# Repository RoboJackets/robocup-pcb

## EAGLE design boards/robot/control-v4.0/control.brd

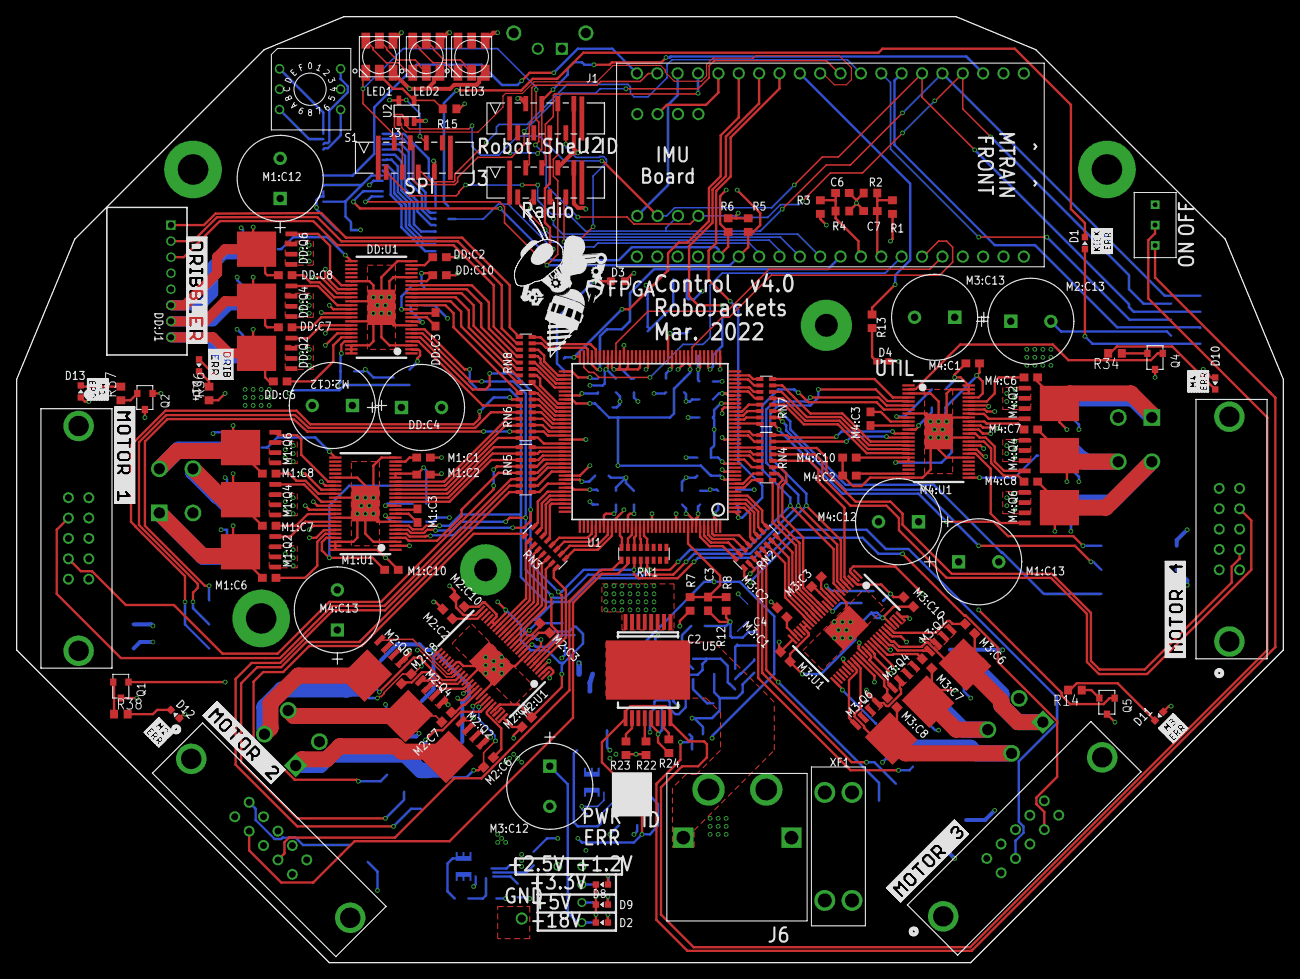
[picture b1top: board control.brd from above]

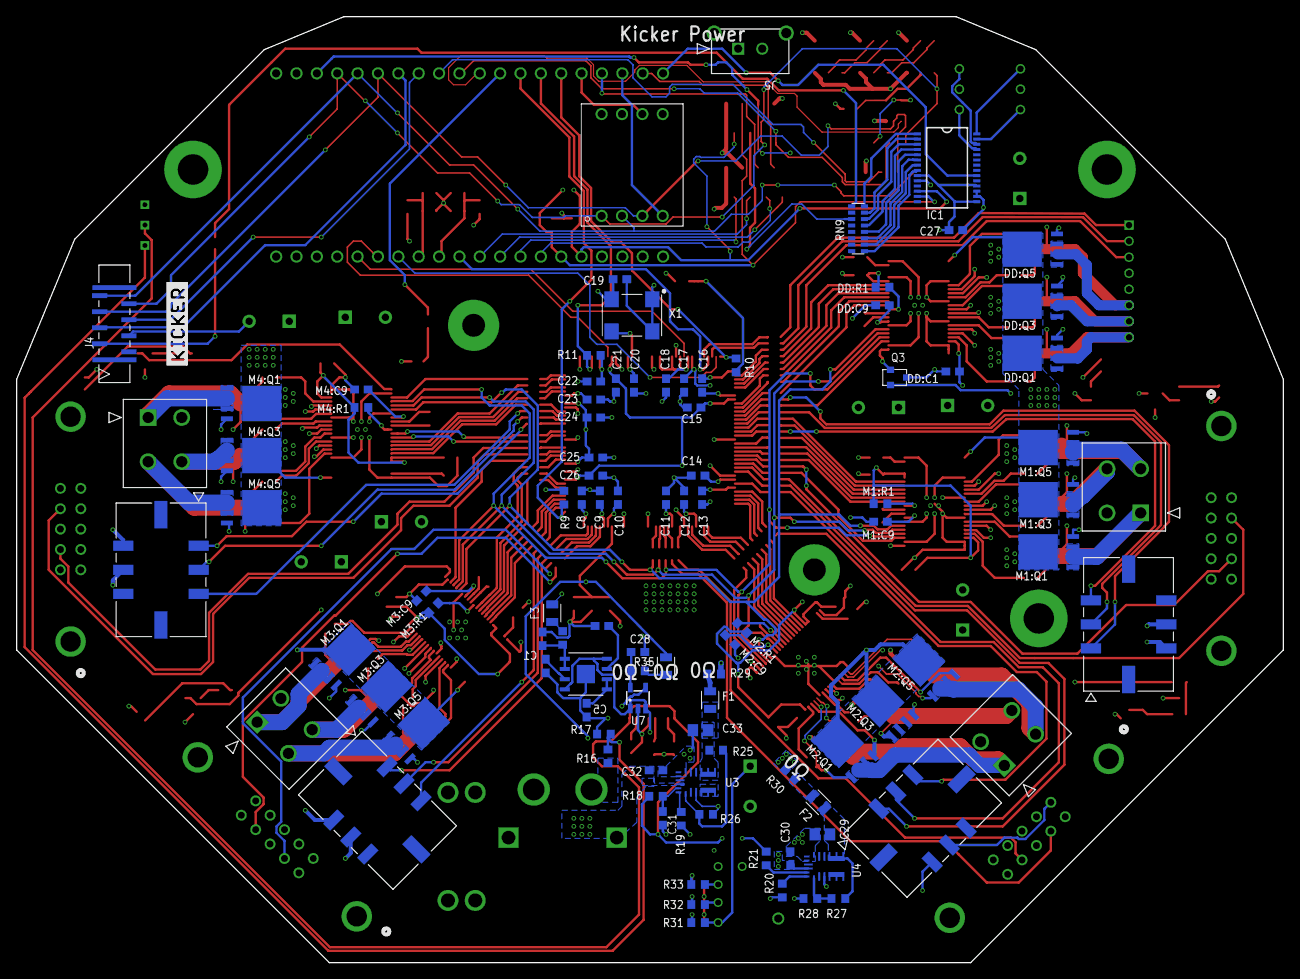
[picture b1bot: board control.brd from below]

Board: 6 copper layers, 158.0 x 118.0 mm, 238 parts (100 on the bottom side), 312 nets.

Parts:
C1, C2, C5, C28: 1uF; C0603
C3, C6, C8, C9, C10, C11, C12, C13, C14, C15, C16, C17, C18, C19, C20, C21, C22, C23, C24, C25, C26, C27: 0.1uF; C0603
C4: 10uF; C0603
C7: 0.1uF 50V; C0603
C29, C33: 22uF 16V; C0805
C30, C32: GRM188R6YA106MA73D; C0603
C31: 2.2uF 50V; C0603
D1, D10, D11, D12, D13, D14: RED; CHIP-LED0603
D2, D8, D9: GREEN; CHIP-LED0603
D3: BLUE; LED-0603
D4: BLUE; CHIP-LED0603
DD:C1, DD:C2: 1uF; C0603
DD:C3: 0.022uF 50V; C0603
DD:C4: ECA-1HHG221; CAP_PAN_10X12.5
DD:C6, DD:C7, DD:C8, DD:C10: 0.1uF 50V; C0603
DD:C9: 2.2uF 50V; C0603
DD:J1: 8-PIN_2MM-H; 2MM-8-H
DD:Q1, DD:Q2, DD:Q3, DD:Q4, DD:Q5, DD:Q6: IRFH7545; PQFN_5X6_E
DD:R1: 10k; R0603
DD:U1: DRV8303DCA; TSSOP-48_PAD
F1, F2, F3, F4: 0805L200SLTHYR; FUSC2113X75
IC1: MCP23017-E/SS; SSOP-28
J1, J2, J3, J4: SFW8S-2STE1LF; CON8_1X8_UB_SFW_JAE
J5: 436500217; CON_436500217_MOL
J6: XT60PW-MAMASS; XT60PW-M
KIT1: MTRAIN; MTRAIN-KIT
KIT2: IMU
LED1, LED2, LED3: APA102C-5050; APA102_5050
M1:C1, M1:C2, M2:C1, M2:C2, M3:C1, M3:C2, M4:C1, M4:C2: 1uF; C0603
M1:C3, M2:C3, M3:C3, M4:C3: 0.022uF 50V; C0603
M1:C6, M1:C7, M1:C8, M1:C10, M2:C6, M2:C7, M2:C8, M2:C10, M3:C6, M3:C7, M3:C8, M3:C10, M4:C6, M4:C7, M4:C8, M4:C10: 0.1uF 50V; C0603
M1:C9, M2:C9, M3:C9, M4:C9: 2.2uF 50V; C0603
M1:C12, M1:C13, M2:C12, M2:C13, M3:C12, M3:C13, M4:C12, M4:C13: ECA-1HHG221; CAP_PAN_10X12.5
M1:J1, M2:J1, M3:J1, M4:J1: 430450618; CON_430450618_MOL
M1:J2, M2:J2, M3:J2, M4:J2: 39288040; CON_39288040
M1:Q1, M1:Q2, M1:Q3, M1:Q4, M1:Q5, M1:Q6, M2:Q1, M2:Q2, M2:Q3, M2:Q4, M2:Q5, M2:Q6, M3:Q1, M3:Q2, M3:Q3, M3:Q4, M3:Q5, M3:Q6, M4:Q1, M4:Q2, M4:Q3, M4:Q4, M4:Q5, M4:Q6: IRFH7545; PQFN_5X6_E
M1:R1, M2:R1, M3:R1, M4:R1: 10k; R0603
M1:U1, M2:U1, M3:U1, M4:U1: DRV8303DCA; TSSOP-48_PAD
M1:U2, M2:U2, M3:U2, M4:U2: N3793-6303RB; N3793-6303RB_3MM
Q1, Q2, Q3, Q4, Q5: PJA3439_R1_00001; SOT-23
R1: 68k 1%; R0603
R2, R3, R4: 10k 1%; R0603
R5, R6, R9, R11: 4.7k; R0603
R7: 68k; R0603
R8, R22: 10k; R0603
R10, R13: 270; R0603
R12, R29, R30, R35: 0; R0603
R14, R34, R36, R37, R38: 330; R0603
R15: 50k; R0603
R16: 270k; R0603
R17: 100k; R0603
R18, R21: 150k; R0603
R19: 43.2k; R0603
R20: 29.4k; R0603
R23, R24, R31, R32, R33: 1k; R0603
R25, R27: 160k 1%; R0603
R26: 30.1k 1%; R0603
R28: 51.0k 1%; R0603
RN1, RN2, RN3, RN4, RN5, RN6, RN7, RN8, RN9: 330; RA-8_2506
S1: 94HCB16T; HEX
S3: TT11EGPC1
U1: XC3S250E-4TQG144C; TQFP144
U2: SN74AHC1G125; SOT-23-5
U3, U4: MPM3620GQV-P
U5: VND5E006ASPTR-E; POWERSO-16
U6: ADP7158ARDZ-1.2-R7ADP7158ARDZ-1.2-R7_ADI-L; ADP7158ARDZ-1.2-R7_ADI-L
U7: MCP1824T-2502E/OT; SOT-23-5
U$1: ERR-DRIB
U$3: MOTOR-1
U$4: DRIBBLER
U$5: MOTOR-2
U$6: MOTOR-3
U$7: MOTOR-4
U$8: ERR-M1
U$9: KICKER
U$11: ROBOBUZZ_1.0X2
U$12: ERR-M2
U$13: ERR-M3
U$14: ERR-M4
U$15: ERR-KICK
X1: ASV-18.432MHZ-EJ-T; ASV
XF1: 30A; 3557-2

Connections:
5V-LED: D9.A, R32.2
5V-LED1: D8.A, R33.2
18.5V-LED: D2.A, R31.1
!CS!-DOT: KIT1.P$11, U2.1
!CS!-FPGA: KIT1.P$31, U1.69
!CS!-ICM: KIT1.P$18, KIT2.4
!CS!-IR: J3.4, KIT1.P$10
!CS!-KICK: J4.5, KIT1.P$8
!CS!-RAD0: J2.4, KIT1.P$17
!RST!-I2C: J1.5, RN9.11
!RST!-IR: J3.5, KIT1.P$9
!RST!-KICK: J4.4, KIT1.P$7
!RST!-RADIO: J2.2, KIT1.P$19
+1.2V: C12.1, C15.1, C21.1, C26.1, F3.2, U1.9, U1.45, U1.80, U1.115
+1.2V-PRE: C4.1, R12.1, U6.1, U6.2
+2.5V: C10.1, C13.1, C17.1, C23.1, F4.2, R9.2, U1.30, U1.65, U1.102, U1.137
+2.5V-PRE: C28.1, R35.1, U7.5
+3.3V: C8.1, C9.1, C11.1, C14.1, C16.1, C18.1, C19.1, C20.1, C22.1, C24.1, C25.1, C27.1, D1.A, D10.A, D11.A, D12.A, D13.A, D14.A, DD:C1.1, DD:C10.1, DD:R1.1, DD:U1.19, DD:U1.45, IC1.9, IC1.15, IC1.18, J3.6, J4.2, KIT2.8, R5.2, R6.2, R11.1, R30.2, R33.1, U1.13, U1.28, U1.42, U1.49, U1.57, U1.60, U1.62, U1.64, U1.79, U1.100, U1.121, U1.138, U1.143, U2.5, U6.4, U6.8, U7.1, U7.3, X1.1, X1.4
+3.3V-FUSE: C29.1, F2.1, R27.2, U4.789
+5V: DD:J1.5, J1.8, J2.6, KIT1.VIN, LED1.1, LED2.1, LED3.1, M1:J1.5, M1:U2.9, M2:J1.5, M2:U2.9, M3:J1.5, M3:U2.9, M4:J1.5, M4:U2.9, R3.1, R29.2, R32.1
+5V-FUSE: C33.1, F1.1, R25.2, U3.789
+18.5V: C30.1, C32.1, DD:C4.1, DD:Q1.5678, DD:Q3.5678, DD:Q5.5678, DD:U1.25, M1:C12.1, M1:C13.1, M1:Q1.5678, M1:Q3.5678, M1:Q5.5678, M1:U1.25, M2:C12.1, M2:C13.1, M2:Q1.5678, M2:Q3.5678, M2:Q5.5678, M2:U1.25, M3:C12.1, M3:C13.1, M3:Q1.5678, M3:Q3.5678, M3:Q5.5678, M3:U1.25, M4:C12.1, M4:C13.1, M4:Q1.5678, M4:Q3.5678, M4:Q5.5678, M4:U1.25, R1.1, R7.1, R31.2, U3.16, U4.16, XF1.3, XF1.4
AAM: R19.2, U3.18
AAM1: R20.2, U4.18
BATT-FPGA: C3.1, R7.2, R8.1, U1.136
BYP: C1.1, U6.3
CS1: R23.2, U5.10
CS2: R24.2, U5.15
CS-DIS: R22.2, U5.12
DD-!CS: DD:U1.4, RN6.11
DD-!FAULT!: DD:U1.2, Q3.1
DD-A-H: DD:U1.13, RN6.9
DD-A-L: DD:U1.14, RN8.16
DD-B-H: DD:U1.15, RN8.15
DD-B-L: DD:U1.16, RN8.14
DD-C-H: DD:U1.17, RN8.13
DD-C-L: DD:U1.18, RN8.12
DD-H1: DD:J1.3, RN8.11
DD-H2: DD:J1.2, RN8.10
DD-H3: DD:J1.1, RN8.9
DD:AVDD: DD:C2.1, DD:U1.23
DD:BST-A: DD:C6.1, DD:U1.44
DD:BST-B: DD:C7.1, DD:U1.39
DD:BST-C: DD:C8.1, DD:U1.34
DD:CP1: DD:C3.1, DD:U1.10
DD:CP2: DD:C3.2, DD:U1.11
DD:EN-GATE: DD:R1.2, DD:U1.12
DD:GH-A: DD:Q1.4, DD:U1.43
DD:GH-B: DD:Q3.4, DD:U1.38
DD:GH-C: DD:Q5.4, DD:U1.33
DD:GL-A: DD:Q2.4, DD:U1.41
DD:GL-B: DD:Q4.4, DD:U1.36
DD:GL-C: DD:Q6.4, DD:U1.31
DD:GVDD: DD:C9.1, DD:U1.9
DD:PHASE-A: DD:C6.2, DD:J1.8, DD:Q1.1, DD:Q1.2, DD:Q1.3, DD:Q2.5678, DD:U1.42
DD:PHASE-B: DD:C7.2, DD:J1.7, DD:Q3.1, DD:Q3.2, DD:Q3.3, DD:Q4.5678, DD:U1.37
DD:PHASE-C: DD:C8.2, DD:J1.6, DD:Q5.1, DD:Q5.2, DD:Q5.3, DD:Q6.5678, DD:U1.32
DOT-CLK-1: LED1.5, R15.2, U2.4
DOT-CLK-1-2: LED1.2, LED2.5
DOT-CLK-2-3: LED2.2, LED3.5
DOT-MOSI-1-2: LED1.3, LED2.4
DOT-MOSI-2-3: LED2.3, LED3.4
EN: C31.1, R18.2, U3.17
EN1: R21.2, U4.17
EN-PWR: R18.1, R21.1, S3.3, U5.9, U5.16
EN-PWR-PRE: R16.1, R17.2, S3.2
EXTRA-IND: KIT1.P$12, R13.1
FB: R25.1, R26.2, U3.1
FB1: R27.1, R28.2, U4.1
FPGA-CLK: U1.50, X1.3
FPGA-DONE: KIT1.P$15, R10.1, U1.72
FPGA-INIT: KIT1.P$14, R11.2, U1.40
FPGA-PROG: KIT1.P$13, R9.1, U1.1
GND: C1.2, C2.2, C3.2, C4.2, C5.2, C6.2, C7.2, C8.2, C9.2, C10.2, C11.2, C12.2, C13.2, C14.2, C15.2, C16.2, C17.2, C18.2, C19.2, C20.2, C21.2, C22.2, C23.2, C24.2, C25.2, C26.2, C27.2, C28.2, C29.2, C30.2, C31.2, C32.2, C33.2, D2.C, D3.C, D4.C, D8.C, D9.C, DD:C1.2, DD:C2.2, DD:C4.2, DD:C9.2, DD:C10.2, DD:J1.4, DD:Q2.1, DD:Q2.2, DD:Q2.3, DD:Q4.1, DD:Q4.2, DD:Q4.3, DD:Q6.1, DD:Q6.2, DD:Q6.3, DD:U1.3, DD:U1.8, DD:U1.20, DD:U1.24, DD:U1.30, DD:U1.35, DD:U1.40, DD:U1.46, DD:U1.47, DD:U1.48, DD:U1.PAD, IC1.10, IC1.16, IC1.17, J1.2, J2.8, J3.7, J4.3, J5.2, J6.P$1, J6.P$3, KIT1.GND, KIT2.5, LED1.6, LED2.6, LED3.6, M1:C1.2, M1:C2.2, M1:C9.2, M1:C10.2, M1:C12.2, M1:C13.2, M1:J1.4, M1:Q2.1, M1:Q2.2, M1:Q2.3, M1:Q4.1, M1:Q4.2, M1:Q4.3, M1:Q6.1, M1:Q6.2, M1:Q6.3, M1:U1.3, M1:U1.8, M1:U1.24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
GPB0: IC1.1, RN9.8
GPB1: IC1.2, RN9.7
GPB2: IC1.3, RN9.6
GPB3: IC1.4, RN9.5
GPB4: IC1.5, RN9.4
GPB5: IC1.6, RN9.3
GPB6: IC1.7, RN9.2
GPB7: IC1.8, RN9.1
HEX-0: IC1.28, S1.1
HEX-1: IC1.25, S1.2
HEX-2: IC1.27, S1.4
HEX-3: IC1.26, S1.8
INT-I2C: J1.4, KIT1.P$3
INT-ICM: KIT1.P$16, KIT2.6
INT-IO: IC1.20, KIT1.P$20
INT-RAD0: J2.5, KIT1.P$30
LED-DD: D14.C, R36.2
LED-KICK: D1.C, RN9.9
LED-M1: D13.C, R37.2
LED-M2: D12.C, R38.2
LED-M3: D11.C, R14.2
LED-M4: D10.C, R34.2
M1-!CS: M1:U1.4, RN5.13
M1-!FAULT!: M1:U1.2, Q2.1
M1-A-H: M1:U1.15, RN5.9
M1-A-L: M1:U1.16, RN6.16
M1-B-H: M1:U1.13, RN5.11
M1-B-L: M1:U1.14, RN5.10
M1-C-H: M1:U1.17, RN6.14
M1-C-L: M1:U1.18, RN6.13
M1-ENC-A: M1:U2.8, RN5.14
M1-ENC-B: M1:U2.4, RN5.12
M1-H1: M1:J1.1, RN6.10
M1-H2: M1:J1.2, RN6.12
M1-H3: M1:J1.3, RN6.15
M1:+3.3V: M1:C1.1, M1:C10.1, M1:R1.1, M1:U1.19, M1:U1.20, M1:U1.45
M1:AVDD: M1:C2.1, M1:U1.23
M1:BST-A: M1:C6.1, M1:U1.44
M1:BST-B: M1:C7.1, M1:U1.39
M1:BST-C: M1:C8.1, M1:U1.34
M1:CP1: M1:C3.1, M1:U1.10
M1:CP2: M1:C3.2, M1:U1.11
M1:EN-GATE: M1:R1.2, M1:U1.12
M1:GH-A: M1:Q1.4, M1:U1.43
M1:GH-B: M1:Q3.4, M1:U1.38
M1:GH-C: M1:Q5.4, M1:U1.33
M1:GL-A: M1:Q2.4, M1:U1.41
M1:GL-B: M1:Q4.4, M1:U1.36
M1:GL-C: M1:Q6.4, M1:U1.31
M1:GVDD: M1:C9.1, M1:U1.9
M1:PHASE-A: M1:C7.2, M1:J2.4, M1:Q3.1, M1:Q3.2, M1:Q3.3, M1:Q4.5678, M1:U1.37
M1:PHASE-B: M1:C6.2, M1:J2.1, M1:Q1.1, M1:Q1.2, M1:Q1.3, M1:Q2.5678, M1:U1.42
M1:PHASE-C: M1:C8.2, M1:J2.3, M1:Q5.1, M1:Q5.2, M1:Q5.3, M1:Q6.5678, M1:U1.32
M2-!CS: M2:U1.4, RN3.16
M2-!FAULT!: M2:U1.2, Q1.1
M2-A-H: M2:U1.15, RN3.13
M2-A-L: M2:U1.16, RN3.12
M2-B-H: M2:U1.13, RN3.15
M2-B-L: M2:U1.14, RN3.14
M2-C-H: M2:U1.17, RN3.11
M2-C-L: M2:U1.18, RN3.10
M2-ENC-A: M2:U2.8, RN1.10
M2-ENC-B: M2:U2.4, RN1.9
M2-H1: M2:J1.1, RN5.15
M2-H2: M2:J1.2, RN5.16
M2-H3: M2:J1.3, RN3.9
M2:+3.3V: M2:C1.1, M2:C10.1, M2:R1.1, M2:U1.19, M2:U1.20, M2:U1.45
M2:AVDD: M2:C2.1, M2:U1.23
M2:BST-A: M2:C6.1, M2:U1.44
M2:BST-B: M2:C7.1, M2:U1.39
M2:BST-C: M2:C8.1, M2:U1.34
M2:CP1: M2:C3.1, M2:U1.10
M2:CP2: M2:C3.2, M2:U1.11
M2:EN-GATE: M2:R1.2, M2:U1.12
M2:GH-A: M2:Q1.4, M2:U1.43
M2:GH-B: M2:Q3.4, M2:U1.38
M2:GH-C: M2:Q5.4, M2:U1.33
M2:GL-A: M2:Q2.4, M2:U1.41
M2:GL-B: M2:Q4.4, M2:U1.36
M2:GL-C: M2:Q6.4, M2:U1.31
M2:GVDD: M2:C9.1, M2:U1.9
M2:PHASE-A: M2:C7.2, M2:J2.4, M2:Q3.1, M2:Q3.2, M2:Q3.3, M2:Q4.5678, M2:U1.37
M2:PHASE-B: M2:C6.2, M2:J2.1, M2:Q1.1, M2:Q1.2, M2:Q1.3, M2:Q2.5678, M2:U1.42
M2:PHASE-C: M2:C8.2, M2:J2.3, M2:Q5.1, M2:Q5.2, M2:Q5.3, M2:Q6.5678, M2:U1.32
M3-!CS: M3:U1.4, RN4.12
M3-!FAULT!: M3:U1.2, Q5.1
M3-A-H: M3:U1.15, RN4.9
M3-A-L: M3:U1.16, RN2.16
M3-B-H: M3:U1.13, RN4.11
M3-B-L: M3:U1.14, RN4.10
M3-C-H: M3:U1.17, RN2.15
M3-C-L: M3:U1.18, RN2.14
M3-ENC-A: M3:U2.8, RN2.10
M3-ENC-B: M3:U2.4, RN2.9
M3-H1: M3:J1.1, RN2.11
M3-H2: M3:J1.2, RN2.12
M3-H3: M3:J1.3, RN2.13
M3:+3.3V: M3:C1.1, M3:C10.1, M3:R1.1, M3:U1.19, M3:U1.20, M3:U1.45
M3:AVDD: M3:C2.1, M3:U1.23
M3:BST-A: M3:C6.1, M3:U1.44
M3:BST-B: M3:C7.1, M3:U1.39
M3:BST-C: M3:C8.1, M3:U1.34
M3:CP1: M3:C3.1, M3:U1.10
M3:CP2: M3:C3.2, M3:U1.11
M3:EN-GATE: M3:R1.2, M3:U1.12
M3:GH-A: M3:Q1.4, M3:U1.43
M3:GH-B: M3:Q3.4, M3:U1.38
M3:GH-C: M3:Q5.4, M3:U1.33
M3:GL-A: M3:Q2.4, M3:U1.41
M3:GL-B: M3:Q4.4, M3:U1.36
M3:GL-C: M3:Q6.4, M3:U1.31
M3:GVDD: M3:C9.1, M3:U1.9
M3:PHASE-A: M3:C7.2, M3:J2.4, M3:Q3.1, M3:Q3.2, M3:Q3.3, M3:Q4.5678, M3:U1.37
M3:PHASE-B: M3:C6.2, M3:J2.1, M3:Q1.1, M3:Q1.2, M3:Q1.3, M3:Q2.5678, M3:U1.42
M3:PHASE-C: M3:C8.2, M3:J2.3, M3:Q5.1, M3:Q5.2, M3:Q5.3, M3:Q6.5678, M3:U1.32
M4-!CS: M4:U1.4, RN7.16
M4-!FAULT!: M4:U1.2, Q4.1
M4-A-H: M4:U1.15, RN7.15
M4-A-L: M4:U1.16, RN7.14
M4-B-H: M4:U1.13, RN4.16
M4-B-L: M4:U1.14, RN4.15
M4-C-H: M4:U1.17, RN7.13
M4-C-L: M4:U1.18, RN7.12
M4-ENC-A: M4:U2.8, RN4.14
M4-ENC-B: M4:U2.4, RN4.13
M4-H1: M4:J1.1, RN7.9
M4-H2: M4:J1.2, RN7.10
M4-H3: M4:J1.3, RN7.11
M4:+3.3V: M4:C1.1, M4:C10.1, M4:R1.1, M4:U1.19, M4:U1.20, M4:U1.45
M4:AVDD: M4:C2.1, M4:U1.23
M4:BST-A: M4:C6.1, M4:U1.44
M4:BST-B: M4:C7.1, M4:U1.39
M4:BST-C: M4:C8.1, M4:U1.34
M4:CP1: M4:C3.1, M4:U1.10
M4:CP2: M4:C3.2, M4:U1.11
M4:EN-GATE: M4:R1.2, M4:U1.12
M4:GH-A: M4:Q1.4, M4:U1.43
M4:GH-B: M4:Q3.4, M4:U1.38
M4:GH-C: M4:Q5.4, M4:U1.33
M4:GL-A: M4:Q2.4, M4:U1.41
M4:GL-B: M4:Q4.4, M4:U1.36
M4:GL-C: M4:Q6.4, M4:U1.31
M4:GVDD: M4:C9.1, M4:U1.9
M4:PHASE-A: M4:C7.2, M4:J2.4, M4:Q3.1, M4:Q3.2, M4:Q3.3, M4:Q4.5678, M4:U1.37
M4:PHASE-B: M4:C6.2, M4:J2.1, M4:Q1.1, M4:Q1.2, M4:Q1.3, M4:Q2.5678, M4:U1.42
M4:PHASE-C: M4:C8.2, M4:J2.3, M4:Q5.1, M4:Q5.2, M4:Q5.3, M4:Q6.5678, M4:U1.32
MISO: J3.1, J4.8, KIT1.P$5, KIT2.2
MISO-AUX: DD:U1.6, M1:U1.6, M2:U1.6, M3:U1.6, M4:U1.6, RN1.12
MISO-FPGA: KIT1.P$35, U1.44
MISO-RADIO: J2.7, KIT1.P$28
MOSI: J3.2, J4.7, KIT1.P$4, KIT2.1, LED1.4
MOSI-AUX: DD:U1.5, M1:U1.5, M2:U1.5, M3:U1.5, M4:U1.5, RN1.11
MOSI-FPGA: KIT1.P$36, U1.63
MOSI-RADIO: J2.3, KIT1.P$27
unnamed: F2.2, R30.1
unnamed: F1.2, R29.1
unnamed: F3.1, R12.2
unnamed: F4.1, R35.2
unnamed: D3.A, R10.2
unnamed: D4.A, R13.2
R-D-DD: Q3.2, R36.1
R-D-M1: Q2.2, R37.1
R-D-M2: Q1.2, R38.1
R-D-M3: Q5.2, R14.1
R-D-M4: Q4.2, R34.1
R-P1: RN8.1, U1.82
R-P2: RN8.2, U1.81
R-P3: RN8.3, U1.77
R-P4: RN8.4, U1.76
R-P5: RN8.5, U1.75
R-P6: RN8.6, U1.74
R-P7: RN8.7, U1.70
R-P8: RN8.8, U1.68
R-P9: RN6.1, U1.91
R-P10: RN6.2, U1.89
R-P11: RN6.3, U1.88
R-P12: RN6.4, U1.87
R-P13: RN6.5, U1.86
R-P14: RN6.6, U1.85
R-P15: RN6.7, U1.84
R-P16: RN6.8, U1.83
R-P17: RN5.1, U1.101
R-P18: RN5.2, U1.98
R-P19: RN5.3, U1.97
R-P20: RN5.4, U1.96
R-P21: RN5.5, U1.95
R-P22: RN5.6, U1.94
R-P23: RN5.7, U1.93
R-P24: RN5.8, U1.92
R-P25: RN3.1, U1.117
R-P26: RN3.2, U1.116
R-P27: RN3.3, U1.113
R-P28: RN3.4, U1.112
R-P29: RN3.5, U1.106
R-P30: RN3.6, U1.105
R-P31: RN3.7, U1.104
R-P32: RN3.8, U1.103
R-P36: RN1.4, U1.125
R-P37: RN1.5, U1.124
R-P38: RN1.6, U1.123
R-P39: RN1.7, U1.122
R-P40: RN1.8, U1.119
R-P41: RN2.1, U1.5
R-P42: RN2.2, U1.4
R-P43: RN2.3, U1.3
R-P44: RN2.4, U1.2
R-P45: RN2.5, U1.142
R-P46: RN2.6, U1.141
R-P47: RN2.7, U1.140
R-P48: RN2.8, U1.139
R-P49: RN4.1, U1.21
R-P50: RN4.2, U1.20
R-P51: RN4.3, U1.17
R-P52: RN4.4, U1.16
R-P53: RN4.5, U1.15
R-P54: RN4.6, U1.14
R-P55: RN4.7, U1.8
R-P56: RN4.8, U1.7
R-P57: RN7.1, U1.35
R-P58: RN7.2, U1.34
R-P59: RN7.3, U1.32
R-P60: RN7.4, U1.31
R-P61: RN7.5, U1.26
R-P62: RN7.6, U1.25
R-P63: RN7.7, U1.24
R-P64: RN7.8, U1.23
REF_NET: C5.1, U6.5, U6.6
SCK: J3.3, J4.6, KIT1.P$6, KIT2.3, U2.2
SCK-AUX: DD:U1.7, M1:U1.7, M2:U1.7, M3:U1.7, M4:U1.7, RN1.13
SCK-FPGA: KIT1.P$34, U1.71
SCK-RADIO: J2.1, KIT1.P$29
SCL: IC1.12, J1.7, KIT1.P$25, R6.1
SDA: IC1.13, J1.6, KIT1.P$26, R5.1
SENSE-BATT: C7.1, KIT1.P$33, R1.2, R2.1
SENSE-VIN: C6.1, KIT1.P$32, R3.2, R4.1
VBATT: J5.1, U5.1, U5.2, U5.3, U5.4, U5.5, U5.6, U5.7, U5.8, XF1.1, XF1.2
VIN: J6.P$2, J6.P$4, R16.2, U5.17
VREG: C2.1, U6.7

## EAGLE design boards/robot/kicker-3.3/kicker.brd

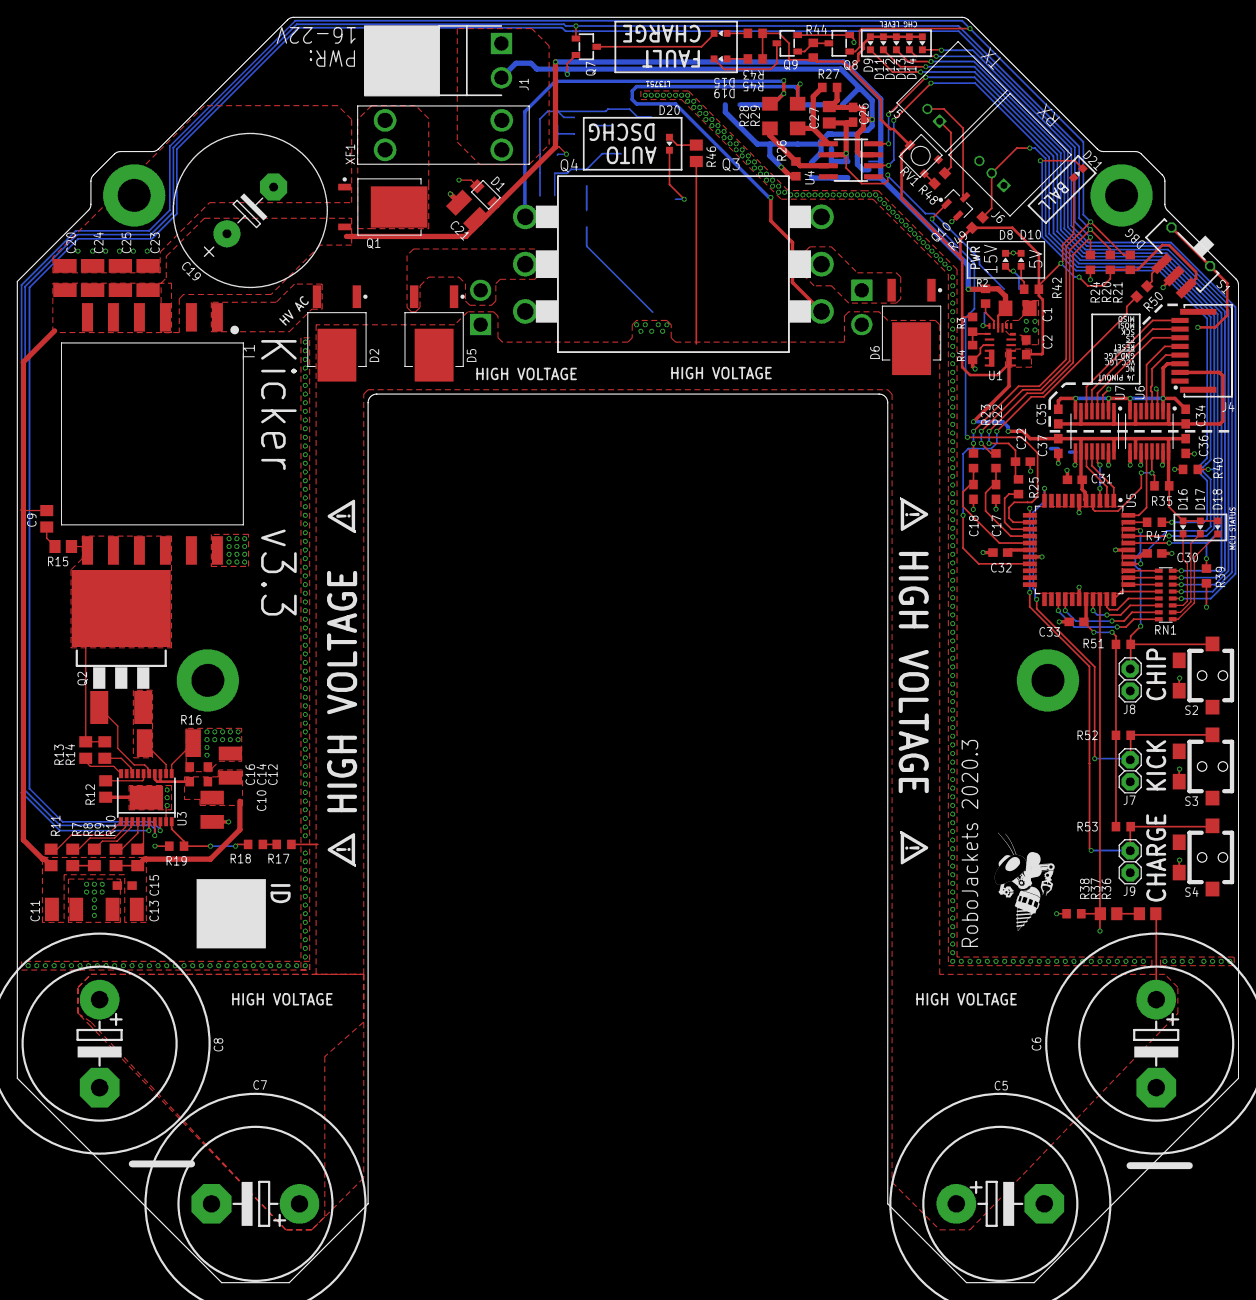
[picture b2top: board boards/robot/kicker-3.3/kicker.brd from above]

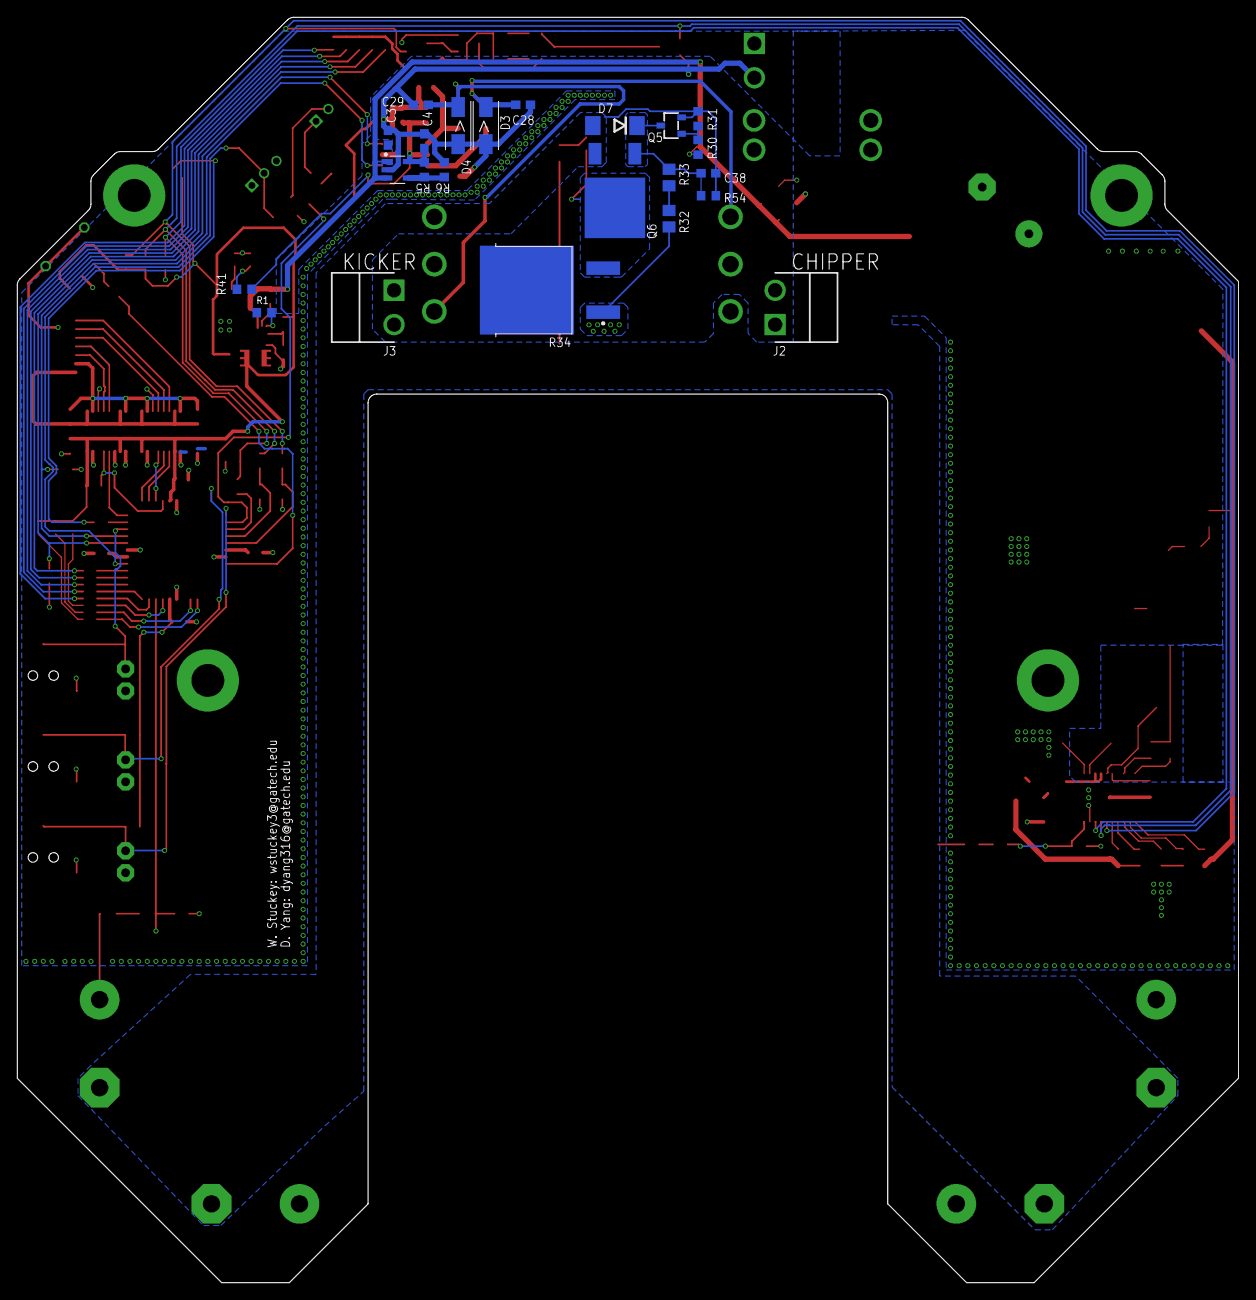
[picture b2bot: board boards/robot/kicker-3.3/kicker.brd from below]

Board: 2 copper layers, 141.0 x 146.1 mm, 152 parts (23 on the bottom side), 94 nets.

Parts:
C1: 10uF 50V; C1206
C2: 22uF 10V; C0603
C3: 1uF 50V; C0603
C4: 2.2uF 35V; C0603
C5, C6, C7, C8: 1000uF; EB25D
C9: 220pF 100V; C0805
C10, C11, C12, C13: 10uF (X7R) 35V; C1210
C14, C15, C16, C26: 0.1uF 35V; C0603
C17, C18, C22: 1uF; C0603
C19: 560uF; E7,5-18
C20, C21, C23, C24, C25: 10uF (X7R); C1210
C27: 22uF 35V; C0805
C28, C29, C38: 0.1uF 50V; C0603
C30, C31, C32, C33, C34, C35, C36, C37: 0.1uF; C0603
D1: PTVS20VS1UR; SOD123-W
D2, D5, D6: VS-5EWH06FN-M3; TO460P990X239-3
D3, D4: SMAJ20A; RESM5226X262
D7: 3SMBJ5929B-TP; DO214AA
D8, D10, D15, D16: GREEN; CHIP-LED0603
D9, D11, D18, D19: RED; CHIP-LED0603
D12, D13, D17, D20: YELLOW; CHIP-LED0603
D14, D21: BLUE; CHIP-LED0603
J1, J2, J3: B2PS-VH(LF)(SN); B2PS-CENTERED
J4: HFW8R-1ST
J5: 2-PIN_2MM-H; 2MM-2-H
J6: 3-PIN_2MM-H; 2MM-3-H
J7: !BTN_KCK_PRE_EXT; 1X2
J8: !BTN_CHP_PRE_EXT; 1X2
J9: !BTN_CHG_PRE_EXT; 1X2
Q1: ATP302ATPAK; TO460P950X150-3
Q2: IRFS4227; D2PAK
Q3, Q4: IXGK400N30A3; TO264
Q5, Q7, Q8, Q9: BSS127; SOT-23-3
Q6: AOD1N60; DPAK
Q10: BSS806NSOT-23-3; SOT95P240X110-3
R1: 43.2k 1%; R0603
R2, R20, R21, R24, R31: 100k; R0603
R3: 160k 1%; R0603
R4: 30.1k 1%; R0603
R5: 110k 1%; R0603
R6: 10k 1%; R0603
R7, R9: 294k 1%; R0805
R8, R10: 412k 1%; R0805
R11, R14: 25.5k 1%; R0805
R12: 1.02k 1%; R0805
R13: 11.5k 1%; R0805
R15: 22; R0805
R16: 7m 1% >1W; R2512
R17: 505k 0.1%; R0603
R18: 113k 0.1%; R0603
R19: 3.0k 0.1%; R0603
R22, R23, R25, R47: 160; R0603
R26, R27, R35, R39, R40, R49, R50, R51, R52, R53: 10k; R0603
R28, R29: 160; R1206
R30: 270k; R0603
R32, R33, R36, R37: ERJ-6GEYJ515V; R0805
R34: 1.5k 35W; TO508P1539X450-3
R38: RC0603FR-07102KL; R0603
R41, R44: 1k; R0603
R42, R43, R45: 330; R0603
R46: ERJ-P06J274V; R0805
R48: 51; R0603
R54: ERJ-6GEYJ106V; R0603
RN1: 330; RA-8_2506
RV1: 500; PVG3G
S1: CSS-121XB
S2, S3, S4: HDP001R
T1: DA203X-ALDA2034; DA2034
U1: MPM3620GQV-P
U2: 15V; SOT95P280X145-5
U3: LT3751FE; TSSOP-20_EP
U4: IX4427N; SOIC-8
U5: AT32ATQFP44; QFP80P1200X1200X120-44
U6: ADUM7441ARQZ-RL7; SOP63P574X165-16
U7: ADUM7441CRQZ-RL7; SOP63P574X165-16
U$1, U$2, U$3, U$4: WARNING2
U$5: ROBOBUZZ_0.6X
XF1: 15A; 3557-2

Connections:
15V_PWR_BR: D8.A, R41.1
!BTN_CHG: J9.1, R53.1, S4.C, U5.12
!BTN_CHP: J8.1, R51.1, S2.C, U5.42
!BTN_KCK: J7.1, R52.1, S3.C, U5.11
!DONE!: C17.1, R22.1, U5.15
!DONE!_RAW: Q7.1, R20.1, R22.2, U3.7
!FAULT!: C18.1, R23.1, U5.16
!FAULT!_RAW: Q8.1, R21.1, R23.2, U3.6
!KICKER_SELECT: U5.44, U6.12
!KICKER_SELECT_EXT: J4.5, U6.5
!RESET: R35.1, U5.4, U6.13
!RESET_EXT: J4.4, U6.4
+5V: C2.1, C30.2, C31.2, C32.2, C33.2, C36.2, C37.2, D9.A, D11.A, D12.A, D13.A, D14.A, D16.A, D17.A, D18.A, D21.A, R3.2, R20.2, R21.2, R35.2, R42.2, R43.2, R44.2, R45.2, R49.2, R51.2, R52.2, R53.2, RV1.P$2, S1.1, U1.789, U5.5, U5.17, U5.27, U5.29, U5.38, U6.10, U6.16, U7.10, U7.16
+15.0V: C4.1, C26.2, C27.2, R5.2, R41.2, U2.5, U4.6
BALL_SENSE: R47.2, U5.43
BALL_SENSE_CL: D21.C, R47.1
BB_RX: J6.2, R49.1, U5.37
BB_TX: Q10.1, U5.13
BB_TX_CL: J5.1, R48.2
CHARGE: R25.1, U5.14
CHARGE_RAW: C22.1, R24.2, R25.2, U3.8
CHIP: R40.2, U4.2, U5.41
CHIPPER: D5.2, J2.2, Q3.C_BOT
CHIP_GATE: R26.2, R28.1, U4.7
CHIP_GATE_S: C28.1, D3.2, Q3.G_BOT, R28.2
CSP: Q2.3, R16.2, U3.12
DISCHARGE_DRAIN: D20.C, Q6.FIN, R34.2
FAULT_INV_BR: Q8.3, Q9.1, R44.1
FB: R3.1, R4.2, U1.1
GND: C1.2, C2.2, C3.2, C4.2, C5.-, C6.-, C7.-, C8.-, C10.2, C11.2, C12.2, C13.2, C14.2, C15.2, C16.2, C17.2, C18.2, C19.-, C20.2, C21.2, C22.2, C23.2, C24.2, C25.2, C26.1, C27.1, C28.2, C29.2, C30.1, C31.1, C32.1, C33.1, C36.1, C37.1, C38.1, D1.A, D3.1, D4.1, D7.A, D8.C, D10.C, J1.2, J6.1, J6.3, J7.2, J8.2, J9.2, Q1.1, Q3.E_BOT, Q4.E_BOT, Q5.2, Q6.3, Q7.2, Q8.2, Q9.2, Q10.2, R1.1, R4.1, R6.1, R12.2, R16.1, R19.2, R24.1, R26.1, R27.1, R31.1, R38.1, R39.1, R40.1, R54.1, S1.2, S1.LEG1, S1.LEG4, S2.B, S3.B, S4.B, T1.12, U1.3, U1.12, U1.13, U1.14, U2.2, U3.9, U3.11, U3.PAD, U4.3, U5.6, U5.18, U5.28, U5.39, U6.3, U6.9, U6.11, U6.15, U7.3, U7.9, U7.15
GND_LGC_EXT: C34.1, C35.1, J4.3, U6.2, U6.8, U7.2, U7.8
HVGATE: Q2.1, U3.15
HV_AC: D2.2, T1.1
HV_FB: R18.2, R19.1, U3.10
HV_IND_HIGH: RN1.10, U5.35
HV_IND_HIGH_CL: D11.C, RN1.7
HV_IND_LOW: RN1.12, U5.33
HV_IND_LOW_CL: D13.C, RN1.5
HV_IND_MAX: RN1.9, U5.36
HV_IND_MAX_CL: D9.C, RN1.8
HV_IND_MID: RN1.11, U5.34
HV_IND_MID_CL: D12.C, RN1.6
HV_IND_MIN: RN1.13, U5.32
HV_IND_MIN_CL: D14.C, RN1.4
HV_SENSE_DIV_BR: R36.1, R37.2
KICK: R39.2, U4.4, U5.40
KICKER: D6.2, J3.1, Q4.C_BOT
KICK_GATE: R27.2, R29.1, U4.5
KICK_GATE_S: C29.1, D4.2, Q4.G_BOT, R29.2
MCU_ERR: RN1.16, U5.25
MCU_ERR_CL: D18.C, RN1.1
MCU_INIT_OK: RN1.14, U5.30
MCU_INIT_OK_CL: D16.C, RN1.3
MCU_MODE: RN1.15, U5.26
MCU_MODE_CL: D17.C, RN1.2
MISO: U5.2, U7.11
MISO_EXT: J4.8, U7.6
MODE_SELECT: R50.2, U5.19
MOSI: U5.1, U7.12
MOSI_EXT: J4.7, U7.5
unnamed: R12.1, U3.16
unnamed: R17.2, R18.1
unnamed: R48.1, RV1.P$3
unnamed: D15.A, R43.1
unnamed: Q1.3, XF1.3, XF1.4
unnamed: R50.1, S1.3
unnamed: R5.1, R6.2, U2.4
unnamed: C9.1, R15.2
unnamed: J5.2, Q10.3
unnamed: D10.A, R42.1
unnamed: R11.1, U3.1
unnamed: D19.A, R45.1
unnamed: D19.C, Q9.3
unnamed: D20.A, R46.1
unnamed: D15.C, Q7.3
unnamed: J1.1, XF1.1, XF1.2
OVLO1: R8.2, U3.3
OVLO2: R10.2, U3.5
QD_GATE_CTRL: Q5.1, R30.1, R31.2
QD_PU_BR: R32.1, R33.2
QUICK_DISCHARGE: C38.2, D7.C, Q5.3, Q6.1, R33.1, R54.2
RDCM: R13.2, U3.20
REG_AAM: R1.2, U1.18
REG_EN: R2.2, U1.17
RVOUT: R14.2, U3.18
SCK: U5.3, U7.13
SCK_EXT: J4.6, U7.4
UVLO1: R7.2, U3.2
UVLO2: R9.2, U3.4
V+: C5.+, C6.+, C7.+, C8.+, D2.3, D5.3, D6.3, J2.1, J3.2, R17.1, R32.2, R34.1, R36.2, R46.2
VBATT: C1.1, C3.1, C9.2, C10.1, C11.1, C12.1, C13.1, C14.1, C15.1, C16.1, C19.+, C20.1, C21.1, C23.1, C24.1, C25.1, D1.C, Q1.2, R2.1, R7.1, R8.1, R9.1, R10.1, R11.2, R30.2, T1.3, T1.4, T1.5, T1.6, U1.16, U2.1, U2.3, U3.13, U3.14
VCC_LGC_EXT: C34.2, C35.2, J4.2, U6.1, U6.7, U7.1, U7.7
VMON: R37.1, R38.2, U5.31
VSN: Q2.2, R13.1, R14.1, R15.1, T1.7, T1.8, T1.9, T1.10

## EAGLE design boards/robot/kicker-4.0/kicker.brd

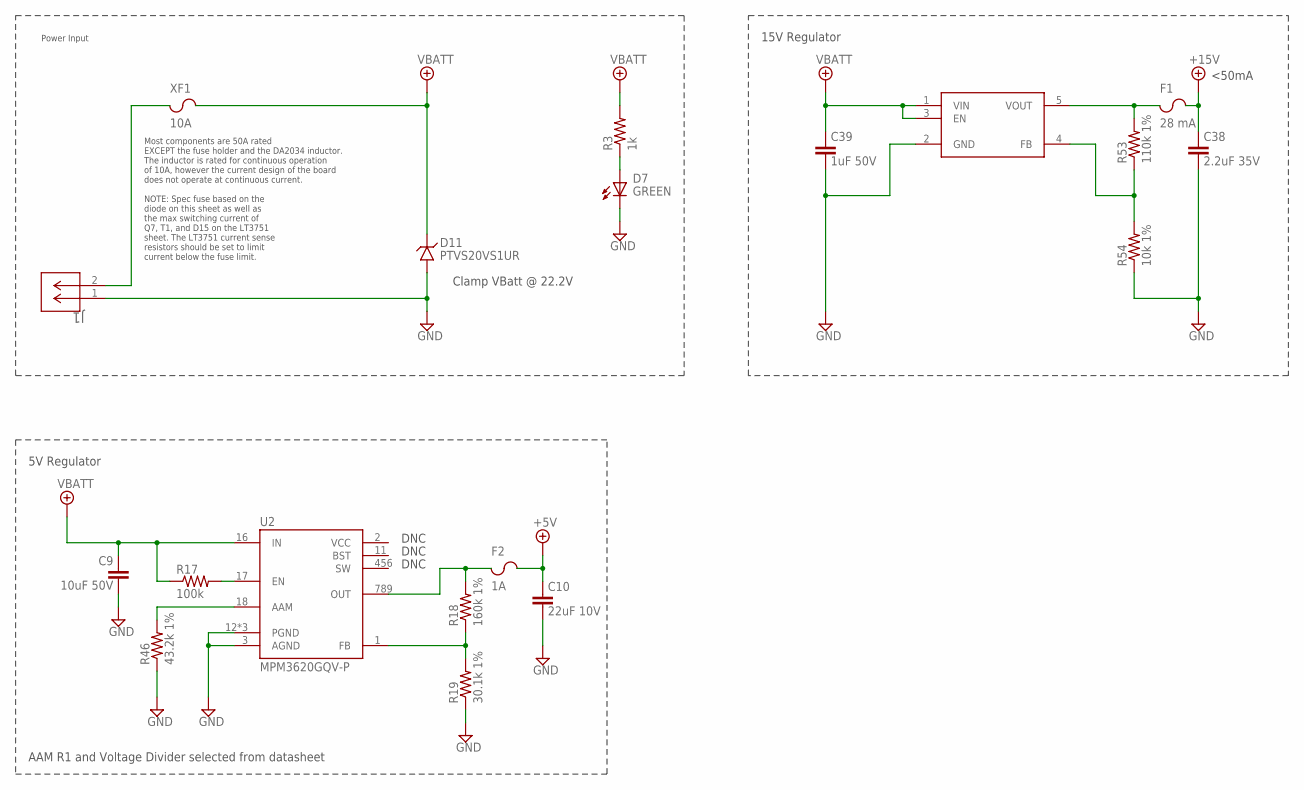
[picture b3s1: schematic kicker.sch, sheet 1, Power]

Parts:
C9: 10uF 50V; C1206
C10: 22uF 10V; C0603
C38: 2.2uF 35V; C0603
C39: 1uF 50V; C0603
D7: GREEN; CHIP-LED0603
D11: PTVS20VS1UR; SOD123-W
F1: 28 mA; F0603
F2: 1A; F0603
J1: 436500217; CON_436500217_MOL
R3: 1k; R0603
R17: 100k; R0603
R18: 160k 1%; R0603
R19: 30.1k 1%; R0603
R46: 43.2k 1%; R0603
R53: 110k 1%; R0603
R54: 10k 1%; R0603
U2: MPM3620GQV-P
U7: 15V; SOT95P280X145-5
XF1: 10A; 3557-2

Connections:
15V_PWR_BR1: D7.A, R3.1
+5V: C10.1, F2.2; also elsewhere on the board
+15V: C38.1, F1.2; also elsewhere on the board
FB: R18.1, R19.2, U2.1 (FB)
GND: C9.2, C10.2, C38.2, C39.2, D7.C (K), D11.A, J1.1, R19.1, R46.1, R54.1, U2.3 (AGND), U2.12 (PGND), U2.13 (PGND), U2.14 (PGND), U7.2 (GND); also elsewhere on the board
unnamed: F1.1, R53.2, U7.5 (VOUT)
unnamed: F2.1, R18.2, U2.789 (OUT)
unnamed: R53.1, R54.2, U7.4 (FB)
unnamed: J1.2, XF1.1, XF1.2 (1)
REG_AAM: R46.2, U2.18 (AAM)
REG_EN: R17.2, U2.17 (EN)
VBATT: C9.1, C39.1, D11.C, R3.2, R17.1, U2.16 (IN), U7.1 (VIN), U7.3 (EN), XF1.3 (2), XF1.4 (2); also elsewhere on the board

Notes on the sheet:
Power Input
5V Regulator
NOTE: Spec fuse based on the diode on this sheet as well as the max switching current of Q7, T1, and D15 on the LT3751 sheet. The LT3751 current sense resistors should be set to limit current below the fuse limit.
15V Regulator
DNC
Clamp VBatt @ 22.2V
<50mA
AAM R1 and Voltage Divider selected from datasheet
Most components are 50A rated EXCEPT the fuse holder and the DA2034 inductor. The inductor is rated for continuous operation of 10A, however the current design of the board does not operate at continuous current.

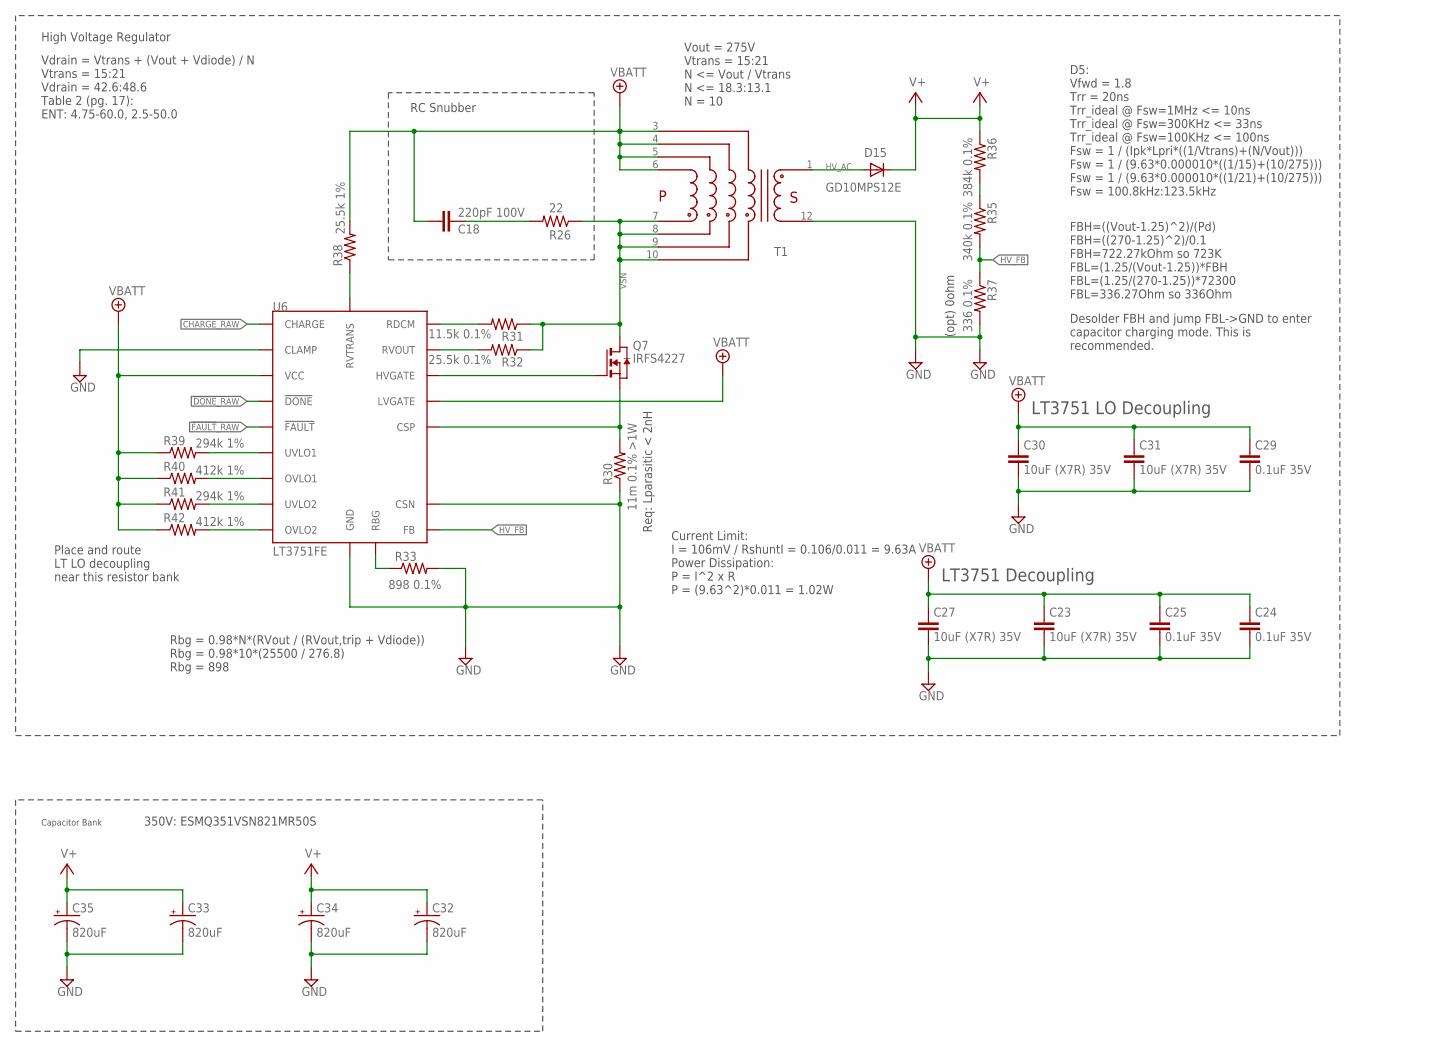
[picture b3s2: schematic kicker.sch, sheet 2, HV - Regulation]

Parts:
C18: 220pF 100V; C0805
C23, C27, C30, C31: 10uF (X7R) 35V; C1210
C24, C25, C29: 0.1uF 35V; C0805
C32, C33, C34, C35: 820uF; EB25D
D15: GD10MPS12E; TO460P990X239-3
Q7: IRFS4227; D2PAK
R26: 22; R0805
R30: 11m 0.1% >1W; R2512
R31: 11.5k 0.1%; R0805
R32: 25.5k 0.1%; R0805
R33: 898 0.1%; R0805
R35: 340k 0.1%; R0603
R36: 384k 0.1%; R0603
R37: 336 0.1%; R0603
R38: 25.5k 1%; R0805
R39, R41: 294k 1%; R0805
R40, R42: 412k 1%; R0805
T1: DA203X-ALDA2034; DA2034
U6: LT3751FE; TSSOP-20_EP

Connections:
!DONE!_RAW: U6.7 (!DONE); also elsewhere on the board
!FAULT!_RAW: U6.6 (!FAULT); also elsewhere on the board
CHARGE_RAW: U6.8 (CHARGE); also elsewhere on the board
CSP: Q7.3 (S), R30.2, U6.12 (CSP)
GND: C23.2, C24.2, C25.2, C27.2, C29.2, C30.2, C31.2, C32.-, C33.-, C34.-, C35.-, R30.1, R33.2, R37.2, T1.12, U6.9 (CLAMP), U6.11 (CSN), U6.PAD (GND); also elsewhere on the board
HVGATE: Q7.1 (G), U6.15 (HVGATE)
HV_AC: D15.2 (A), T1.1
HV_FB: R35.2, R37.1, U6.10 (FB)
unnamed: R33.1, U6.16 (RBG)
unnamed: R35.1, R36.2
unnamed: C18.1, R26.2
unnamed: R38.1, U6.1 (RVTRANS)
OVLO1: R40.2, U6.3 (OVLO1)
OVLO2: R42.2, U6.5 (OVLO2)
RDCM: R31.2, U6.20 (RDCM)
RVOUT: R32.2, U6.18 (RVOUT)
UVLO1: R39.2, U6.2 (UVLO1)
UVLO2: R41.2, U6.4 (UVLO2)
V+: C32.+, C33.+, C34.+, C35.+, D15.3 (C), R36.1; also elsewhere on the board
VBATT: C18.2, C23.1, C24.1, C25.1, C27.1, C29.1, C30.1, C31.1, R38.2, R39.1, R40.1, R41.1, R42.1, T1.3, T1.4, T1.5, T1.6, U6.13 (VCC), U6.14 (LVGATE); also elsewhere on the board
VSN: Q7.2 (D), R26.1, R31.1, R32.1, T1.7, T1.8, T1.9, T1.10

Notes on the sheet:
Capacitor Bank
High Voltage Regulator
350V: ESMQ351VSN821MR50S
RC Snubber
LT3751 LO Decoupling
LT3751 Decoupling
Place and route LT LO decoupling near this resistor bank
Desolder FBH and jump FBL->GND to enter capacitor charging mode. This is recommended.
(opt) 0ohm
Current Limit: I = 106mV / RshuntI = 0.106/0.011 = 9.63A Power Dissipation: P = I^2 x R P = (9.63^2)*0.011 = 1.02W
Req: Lparasitic < 2nH
Rbg = 0.98*N*(RVout / (RVout,trip + Vdiode)) Rbg = 0.98*10*(25500 / 276.8) Rbg = 898
Vout = 275V Vtrans = 15:21 N <= Vout / Vtrans N <= 18.3:13.1 N = 10
D5: Vfwd = 1.8 Trr = 20ns Trr_ideal @ Fsw=1MHz <= 10ns Trr_ideal @ Fsw=300KHz <= 33ns Trr_ideal @ Fsw=100KHz <= 100ns Fsw = 1 / (Ipk*Lpri*((1/Vtrans)+(N/Vout))) Fsw = 1 / (9.63*0.000010*((1/15)+(10/275))) Fsw = 1 / (9.63*0.000010*((1/21)+(10/275))) Fsw = 100.8kHz:123.5kHz
FBH=((Vout-1.25)^2)/(Pd) FBH=((270-1.25)^2)/0.1 FBH=722.27kOhm so 723K FBL=(1.25/(Vout-1.25))*FBH FBL=(1.25/(270-1.25))*72300 FBL=336.27Ohm so 336Ohm
Vdrain = Vtrans + (Vout + Vdiode) / N Vtrans = 15:21 Vdrain = 42.6:48.6 Table 2 (pg. 17): ENT: 4.75-60.0, 2.5-50.0

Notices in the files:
parts and their libraries:
SparkFun-Connectors: Licensing: Creative Commons ShareAlike 4.0 International - https://creativecommons.org/licenses/by-sa/4.0
COPYRIGHT: Copyright (C) 2022 Ultra Librarian. All rights reserved.
